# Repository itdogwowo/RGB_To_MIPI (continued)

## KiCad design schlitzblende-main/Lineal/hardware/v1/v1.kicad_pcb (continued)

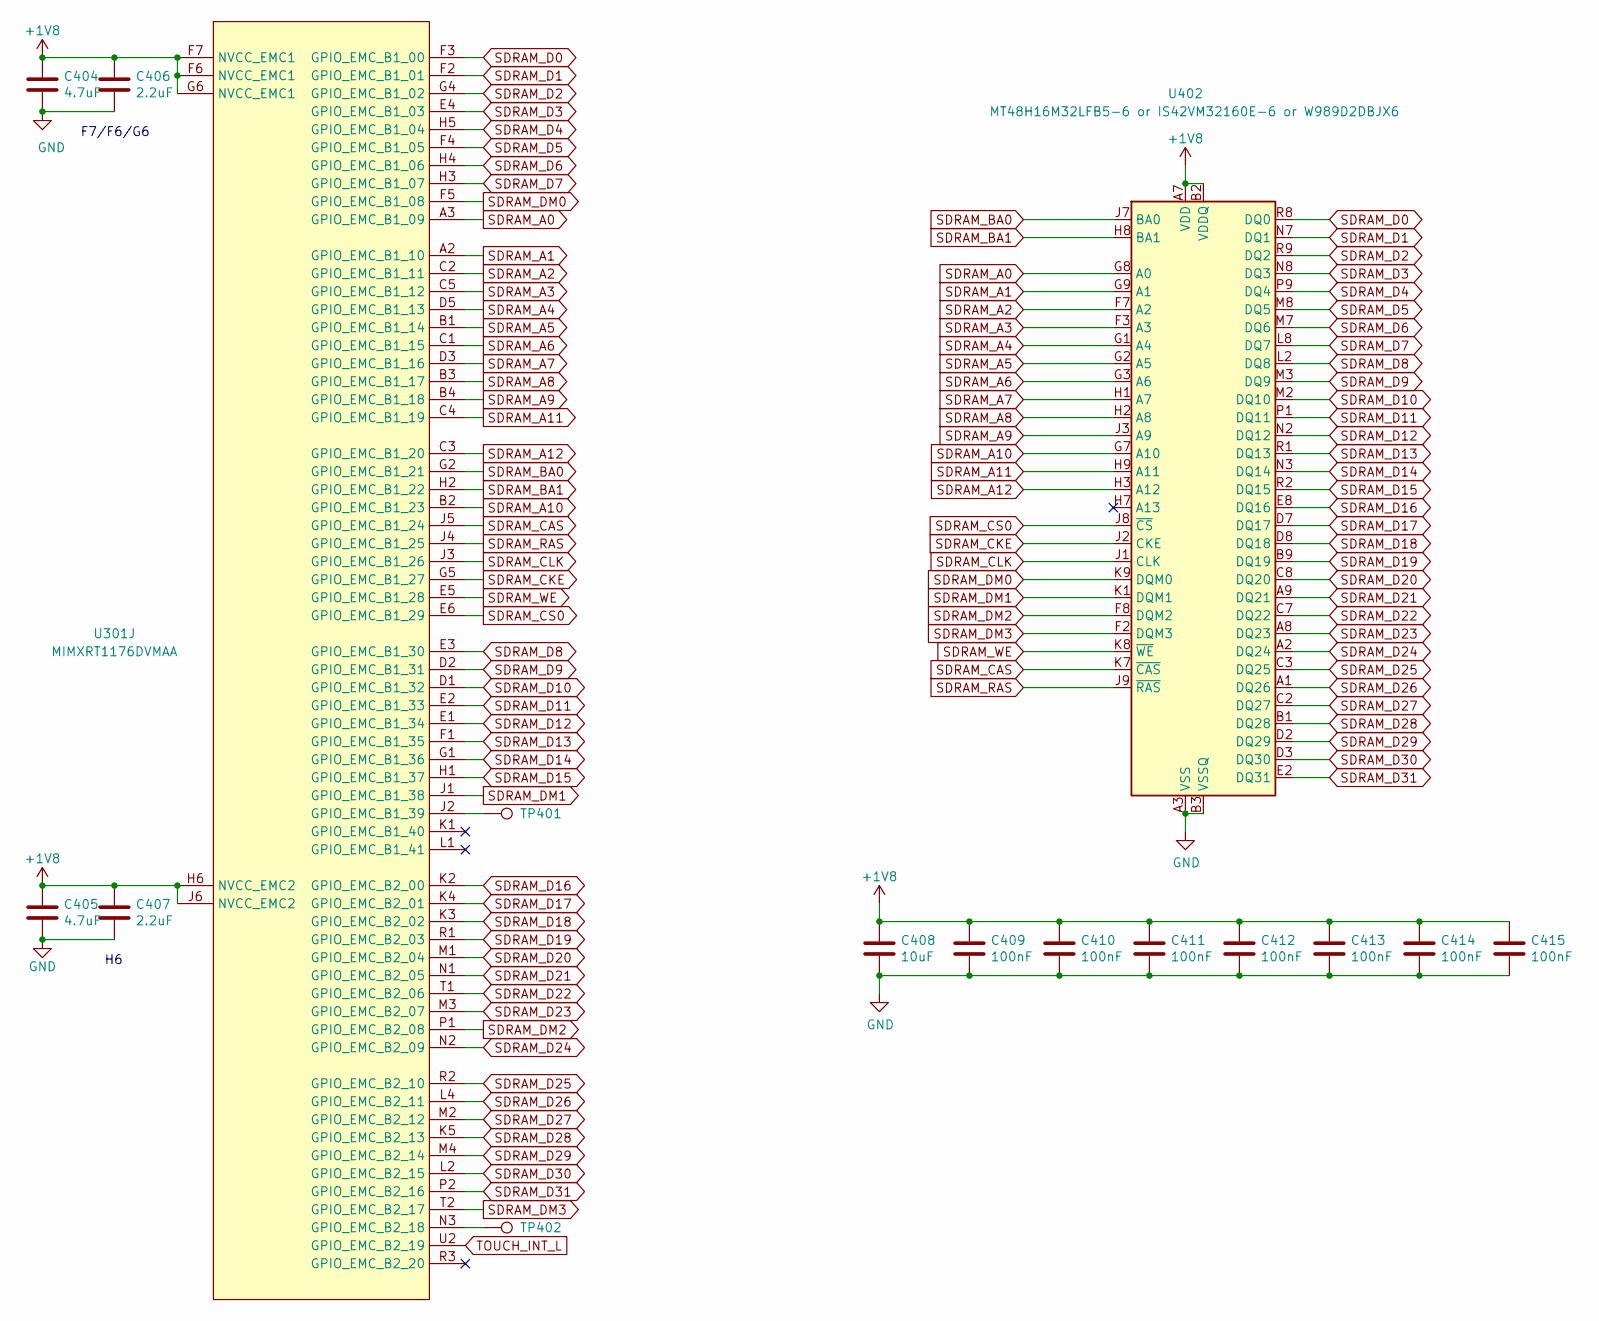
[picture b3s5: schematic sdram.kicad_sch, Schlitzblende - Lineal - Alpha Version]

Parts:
C404, C405: 4.7uF; C_0402_1005Metric
C406, C407: 2.2uF; C_0402_1005Metric
C408: 10uF; C_0402_1005Metric
C409, C410, C411, C412, C413, C414, C415: 100nF; C_0402_1005Metric
TP401: DQS; TestPoint_Pad_D0.5mm
TP402: DQS4; TestPoint_Pad_D0.5mm
U301: MIMXRT1176DVMAA; BGA-289_17x17_14.0x14.0mm
U402: MT48H16M32LFB5-6 or IS42VM32160E-6 or W989D2DBJX6; BGA-90_9x15_8.0x13.0mm

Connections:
+1V8: C404.1, C405.1, C406.1, C407.1, C408.1, C409.1, C410.1, C411.1, C412.1, C413.1, C414.1, C415.1, U301.F6 (NVCC_EMC1), U301.F7 (NVCC_EMC1), U301.G6 (NVCC_EMC1), U301.H6 (NVCC_EMC2), U301.J6 (NVCC_EMC2), U402.A7 (VDD), U402.B2 (VDDQ), U402.B7 (VDDQ), U402.C9 (VDDQ), U402.D9 (VDDQ), U402.E1 (VDDQ), U402.F9 (VDD), U402.L1 (VDDQ), U402.L7 (VDD), U402.M9 (VDDQ), U402.N9 (VDDQ), U402.P2 (VDDQ), U402.P7 (VDDQ), U402.R7 (VDD); also elsewhere on the board
unnamed: TP402.1, U301.N3 (GPIO_EMC_B2_18)
SDRAM_A0: U301.A3 (GPIO_EMC_B1_09), U402.G8 (A0)
SDRAM_A1: U301.A2 (GPIO_EMC_B1_10), U402.G9 (A1)
SDRAM_A2: U301.C2 (GPIO_EMC_B1_11), U402.F7 (A2)
SDRAM_A3: U301.C5 (GPIO_EMC_B1_12), U402.F3 (A3)
SDRAM_A4: U301.D5 (GPIO_EMC_B1_13), U402.G1 (A4)
SDRAM_A5: U301.B1 (GPIO_EMC_B1_14), U402.G2 (A5)
SDRAM_A6: U301.C1 (GPIO_EMC_B1_15), U402.G3 (A6)
SDRAM_A7: U301.D3 (GPIO_EMC_B1_16), U402.H1 (A7)
SDRAM_A8: U301.B3 (GPIO_EMC_B1_17), U402.H2 (A8)
SDRAM_A9: U301.B4 (GPIO_EMC_B1_18), U402.J3 (A9)
SDRAM_A10: U301.B2 (GPIO_EMC_B1_23), U402.G7 (A10)
SDRAM_A11: U301.C4 (GPIO_EMC_B1_19), U402.H9 (A11)
SDRAM_A12: U301.C3 (GPIO_EMC_B1_20), U402.H3 (A12)
SDRAM_BA0: U301.G2 (GPIO_EMC_B1_21), U402.J7 (BA0)
SDRAM_BA1: U301.H2 (GPIO_EMC_B1_22), U402.H8 (BA1)
SDRAM_CAS: U301.J5 (GPIO_EMC_B1_24), U402.K7 (~CAS)
SDRAM_CKE: U301.G5 (GPIO_EMC_B1_27), U402.J2 (CKE)
SDRAM_CLK: U301.J3 (GPIO_EMC_B1_26), U402.J1 (CLK)
SDRAM_CS0: U301.E6 (GPIO_EMC_B1_29), U402.J8 (~CS)
SDRAM_D0: U301.F3 (GPIO_EMC_B1_00), U402.R8 (DQ0)
SDRAM_D1: U301.F2 (GPIO_EMC_B1_01), U402.N7 (DQ1)
SDRAM_D2: U301.G4 (GPIO_EMC_B1_02), U402.R9 (DQ2)
SDRAM_D3: U301.E4 (GPIO_EMC_B1_03), U402.N8 (DQ3)
SDRAM_D4: U301.H5 (GPIO_EMC_B1_04), U402.P9 (DQ4)
SDRAM_D5: U301.F4 (GPIO_EMC_B1_05), U402.M8 (DQ5)
SDRAM_D6: U301.H4 (GPIO_EMC_B1_06), U402.M7 (DQ6)
SDRAM_D7: U301.H3 (GPIO_EMC_B1_07), U402.L8 (DQ7)
SDRAM_D8: U301.E3 (GPIO_EMC_B1_30), U402.L2 (DQ8)
SDRAM_D9: U301.D2 (GPIO_EMC_B1_31), U402.M3 (DQ9)
SDRAM_D10: U301.D1 (GPIO_EMC_B1_32), U402.M2 (DQ10)
SDRAM_D11: U301.E2 (GPIO_EMC_B1_33), U402.P1 (DQ11)
SDRAM_D12: U301.E1 (GPIO_EMC_B1_34), U402.N2 (DQ12)
SDRAM_D13: U301.F1 (GPIO_EMC_B1_35), U402.R1 (DQ13)
SDRAM_D14: U301.G1 (GPIO_EMC_B1_36), U402.N3 (DQ14)
SDRAM_D15: U301.H1 (GPIO_EMC_B1_37), U402.R2 (DQ15)
SDRAM_D16: U301.K2 (GPIO_EMC_B2_00), U402.E8 (DQ16)
SDRAM_D17: U301.K4 (GPIO_EMC_B2_01), U402.D7 (DQ17)
SDRAM_D18: U301.K3 (GPIO_EMC_B2_02), U402.D8 (DQ18)
SDRAM_D19: U301.R1 (GPIO_EMC_B2_03), U402.B9 (DQ19)
SDRAM_D20: U301.M1 (GPIO_EMC_B2_04), U402.C8 (DQ20)
SDRAM_D21: U301.N1 (GPIO_EMC_B2_05), U402.A9 (DQ21)
SDRAM_D22: U301.T1 (GPIO_EMC_B2_06), U402.C7 (DQ22)
SDRAM_D23: U301.M3 (GPIO_EMC_B2_07), U402.A8 (DQ23)
SDRAM_D24: U301.N2 (GPIO_EMC_B2_09), U402.A2 (DQ24)
SDRAM_D25: U301.R2 (GPIO_EMC_B2_10), U402.C3 (DQ25)
SDRAM_D26: U301.L4 (GPIO_EMC_B2_11), U402.A1 (DQ26)
SDRAM_D27: U301.M2 (GPIO_EMC_B2_12), U402.C2 (DQ27)
SDRAM_D28: U301.K5 (GPIO_EMC_B2_13), U402.B1 (DQ28)
SDRAM_D29: U301.M4 (GPIO_EMC_B2_14), U402.D2 (DQ29)
SDRAM_D30: U301.L2 (GPIO_EMC_B2_15), U402.D3 (DQ30)
SDRAM_D31: U301.P2 (GPIO_EMC_B2_16), U402.E2 (DQ31)
SDRAM_DM0: U301.F5 (GPIO_EMC_B1_08), U402.K9 (DQM0)
SDRAM_DM1: U301.J1 (GPIO_EMC_B1_38), U402.K1 (DQM1)
SDRAM_DM2: U301.P1 (GPIO_EMC_B2_08), U402.F8 (DQM2)
SDRAM_DM3: U301.T2 (GPIO_EMC_B2_17), U402.F2 (DQM3)
SDRAM_RAS: U301.J4 (GPIO_EMC_B1_25), U402.J9 (~RAS)
SDRAM_WE: U301.E5 (GPIO_EMC_B1_28), U402.K8 (~WE)
TOUCH_INT_L: U301.U2 (GPIO_EMC_B2_19); also elsewhere on the board

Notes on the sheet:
F7/F6/G6

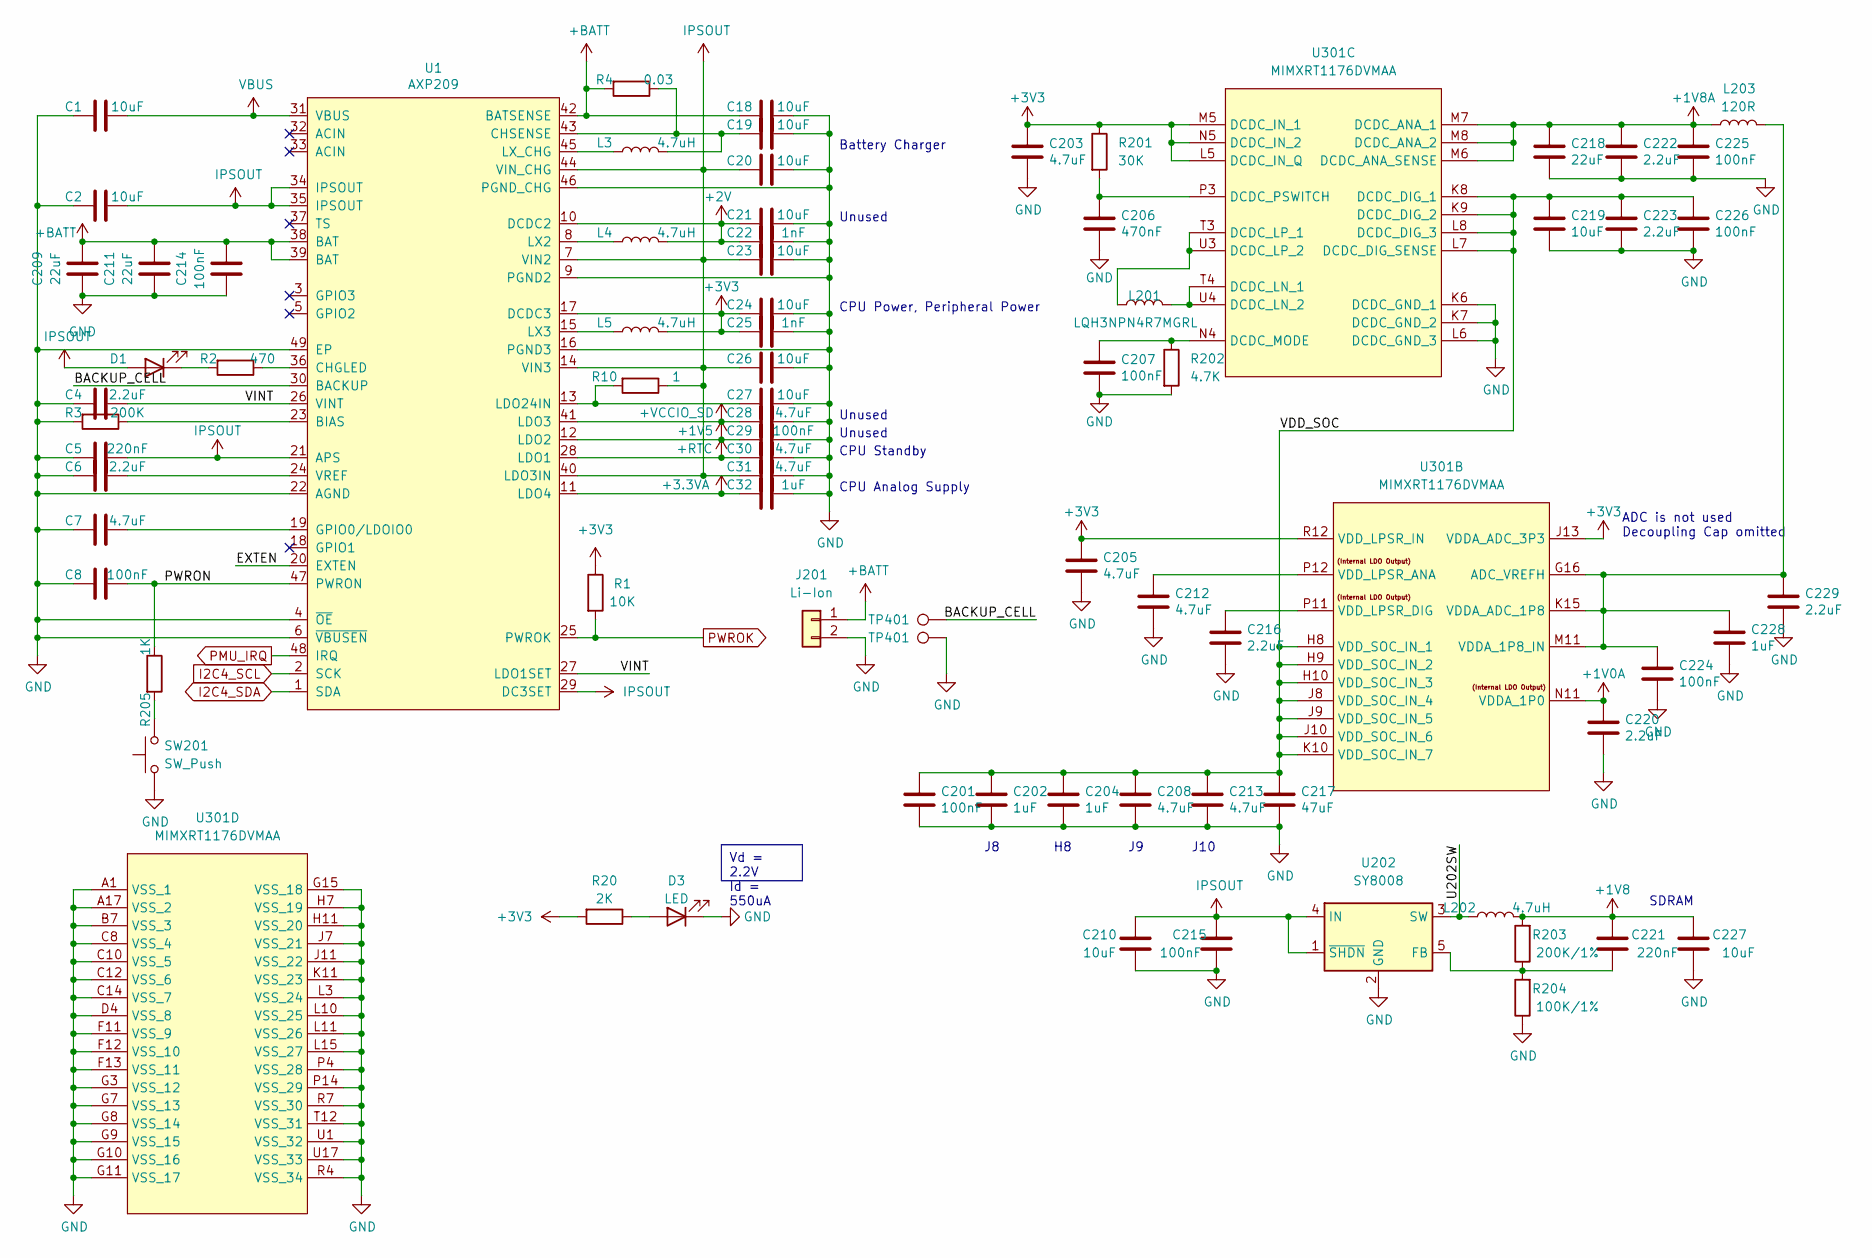
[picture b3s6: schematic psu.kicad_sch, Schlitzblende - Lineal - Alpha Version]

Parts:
C1, C2, C18, C19, C20, C21, C23, C24, C26, C27: 10uF; C_0603_1608Metric
C4, C6, C216, C220, C222, C223, C229: 2.2uF; C_0402_1005Metric
C5: 220nF; C_0402_1005Metric
C7, C28, C30, C31, C203, C205, C208, C212, C213: 4.7uF; C_0402_1005Metric
C8, C29, C201, C207, C224, C225, C226: 100nF; C_0402_1005Metric
C22, C25: 1nF; C_0402_1005Metric
C32, C202, C204, C228: 1uF; C_0402_1005Metric
C206: 470nF; C_0402_1005Metric
C209, C211: 22uF; C_0603_1608Metric; LCSC C116413
C210, C227: 10uF; C_0603_1608Metric; LCSC C105490
C214, C215: 100nF; C_0402_1005Metric; LCSC C56392
C217: 47uF; C_0603_1608Metric
C218: 22uF; C_0603_1608Metric
C219: 10uF; C_0402_1005Metric
C221: 220nF; C_0402_1005Metric; LCSC C880414
D1, D3: LED; D_0402_1005Metric
J201: Li-Ion; JST_ACH_BM02B-ACHSS-GAN-ETF_1x02-1MP_P1.20mm_Vertical
L3, L4, L5: 4.7uH; L_1212
L201: LQH3NPN4R7MGRL; L_1008_2520Metric
L202: 4.7uH; L_1212; LCSC C340379
L203: 120R; L_0402_1005Metric
R1: 10K; R_0402_1005Metric
R2: 470; R_0402_1005Metric
R3: 200K; R_0402_1005Metric
R4: 0.03; R_0402_1005Metric
R10: 1; R_0603_1608Metric
R20: 2K; R_0402_1005Metric
R201: 30K; R_0402_1005Metric
R202: 4.7K; R_0402_1005Metric
R203: 200K/1%; R_0402_1005Metric; LCSC C327350
R204: 100K/1%; R_0402_1005Metric; LCSC C138022
R205: 1K; R_0402_1005Metric
SW201: SW_Push; SW_SPST_TL3342
TP401: DQS; TestPoint_Pad_D0.5mm
U1: AXP209; QFN-48-1EP_6x6mm_P0.4mm_EP4.2x4.2mm_ThermalVias
U202: SY8008; TSOT-23-5; LCSC C82161
U301: MIMXRT1176DVMAA; BGA-289_17x17_14.0x14.0mm

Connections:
+1V0A: C220.1, U301.N11 (VDDA_1P0); also elsewhere on the board
+1V5: C29.2, U1.12 (LDO2)
+1V8: C221.2, C227.2, L202.2, R203.2; also elsewhere on the board
+1V8A: C218.1, C222.1, C225.1, L203.1, U301.M6 (DCDC_ANA_SENSE), U301.M7 (DCDC_ANA_1), U301.M8 (DCDC_ANA_2); also elsewhere on the board
+2V: C21.2, C22.2, L4.2, U1.10 (DCDC2)
+3.3VA: C32.2, U1.11 (LDO4)
+BATT: C18.2, C209.1, C211.1, C214.1, J201.1, R4.2, U1.38 (BAT), U1.39 (BAT), U1.42 (BATSENSE); also elsewhere on the board
+VCCIO_SD: C28.2, U1.41 (LDO3); also elsewhere on the board
/PSU/EXTEN: U1.20 (EXTEN)
/PSU/PWRON: C8.1, R205.1, U1.47 (PWRON)
/PSU/U202SW: L202.1, U202.3 (SW)
/PSU/VDD_SOC: C201.1, C202.1, C204.1, C208.1, C213.1, C217.1, C219.1, C223.1, C226.1, U301.H8 (VDD_SOC_IN_1), U301.H9 (VDD_SOC_IN_2), U301.H10 (VDD_SOC_IN_3), U301.J8 (VDD_SOC_IN_4), U301.J9 (VDD_SOC_IN_5), U301.J10 (VDD_SOC_IN_6), U301.K8 (DCDC_DIG_1), U301.K9 (DCDC_DIG_2), U301.K10 (VDD_SOC_IN_7), U301.L7 (DCDC_DIG_SENSE), U301.L8 (DCDC_DIG_3)
/PSU/VINT: C4.1, U1.26 (VINT), U1.27 (LDO1SET)
I2C4_SCL: U1.2 (SCK); also elsewhere on the board
I2C4_SDA: U1.1 (SDA); also elsewhere on the board
IPSOUT: C2.1, C5.1, C20.2, C23.2, C26.2, C31.2, C210.2, C215.2, D1.2 (A), R10.1, U1.7 (VIN2), U1.14 (VIN3), U1.21 (APS), U1.29 (DC3SET), U1.34 (IPSOUT), U1.35 (IPSOUT), U1.40 (LDO3IN), U1.44 (VIN_CHG), U202.1 (~SHDN), U202.4 (IN)
unnamed: D1.1 (K), R2.2
unnamed: D3.2 (A), R20.1
unnamed: R3.1, U1.23 (BIAS)
unnamed: R2.1, U1.36 (CHGLED)
unnamed: C19.2, L3.2, R4.1, U1.43 (CHSENSE)
unnamed: C7.1, U1.19 (GPIO0/LDOIO0)
unnamed: C27.2, R10.2, U1.13 (LDO24IN)
unnamed: L4.1, U1.8 (LX2)
unnamed: L5.1, U1.15 (LX3)
unnamed: L3.1, U1.45 (LX_CHG)
unnamed: C6.1, U1.24 (VREF)
unnamed: C221.1, R203.1, R204.2, U202.5 (FB)
unnamed: C224.1, C228.1, C229.1, L203.2, U301.G16 (ADC_VREFH), U301.K15 (VDDA_ADC_1P8), U301.M11 (VDDA_1P8_IN)
unnamed: C212.1, U301.P12 (VDD_LPSR_ANA)
unnamed: C216.1, U301.P11 (VDD_LPSR_DIG)
unnamed: L201.2, U301.T4 (DCDC_LN_1), U301.U4 (DCDC_LN_2)
unnamed: L201.1, U301.T3 (DCDC_LP_1), U301.U3 (DCDC_LP_2)
unnamed: C207.1, R202.1, U301.N4 (DCDC_MODE)
unnamed: C206.1, R201.2, U301.P3 (DCDC_PSWITCH)
PMU_IRQ: U1.48 (IRQ); also elsewhere on the board
PWROK: R1.2, U1.25 (PWROK); also elsewhere on the board
VBUS: C1.1, U1.31 (VBUS); also elsewhere on the board

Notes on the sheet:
Vd = 2.2V Id = 550uA
Unused
CPU Standby
Battery Charger
J10
SDRAM
CPU Power, Peripheral Power
ADC is not used Decoupling Cap omitted
CPU Analog Supply

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
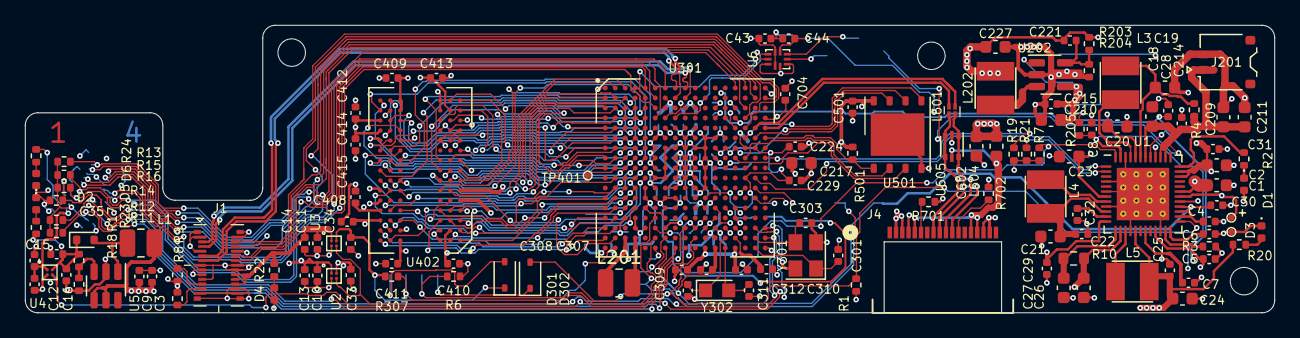
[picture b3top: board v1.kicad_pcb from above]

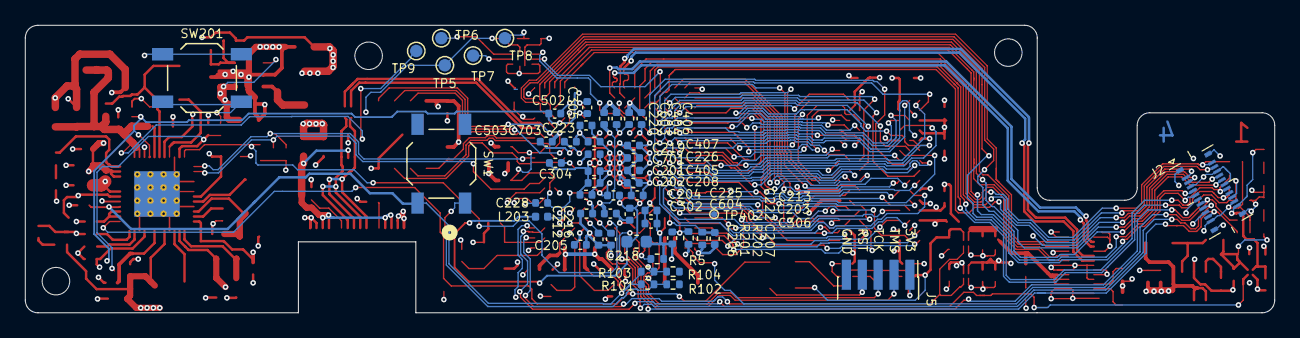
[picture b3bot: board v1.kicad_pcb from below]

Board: 4 copper layers, 100.0 x 23.0 mm, 184 parts (51 on the bottom side), 165 nets.

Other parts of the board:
C16: 1uF; C_0402_1005Metric
D4, D5, D6: LED; D_0402_1005Metric
R22: 2K; R_0402_1005Metric
R23, R24: 3.3K; R_0402_1005Metric
SW1: SW_Push; SW_SPST_TL3342
TP1, TP2: DQS; TestPoint_Pad_D0.5mm

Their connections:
unnamed: D4.2 (A), R22.1
unnamed: D5.2 (A), R23.1
unnamed: D6.2 (A), R24.1

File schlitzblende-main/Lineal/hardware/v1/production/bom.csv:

Designator,Footprint,Quantity,Value,LCSC Part #
"C1, C18, C19, C2, C20, C21, C210, C227, C23, C24, C26, C27, C602",0603,13,10uF,
"C10, C11, C12, C16, C202, C204, C228, C3, C307, C308, C32, C603, C604, C701, C703, C704",0402,16,1uF,
"C13, C14, C15, C33, C34, C35",0402,6,0.1uF,
"C201, C207, C214, C215, C224, C225, C226, C29, C312, C409, C410, C411, C412, C413, C414, C415, C43, C44, C8, C9",0402,20,100nF,
"C203, C205, C208, C212, C213, C28, C30, C31, C404, C405, C7",0402,11,4.7uF,
"C206, C310, C501",0402,3,470nF,
"C209, C211, C218",0603,3,22uF,C116413
"C216, C220, C222, C223, C229, C302, C304, C305, C306, C4, C406, C407, C502, C503, C6",0402,15,2.2uF,
C217,0603,1,47uF,
"C219, C408",0402,2,10uF,
"C22, C25",0402,2,1nF,
"C221, C5",0402,2,220nF,C880414
"C301, C303, C309, C311",0402,4,18pF,
"D1, D3, D4, D5, D6",0402,5,LED,
D2,D_SOD-523,1,B0530WS,
"D301, D302",D_SOD-323,2,B0540W,
"H1, H3, H4",MountingHole_2.2mm_M2_DIN965,3,MountingHole,
J1,DF40PG(1.5)-26DS-04V,1,DF40PG(1.5)-26DS-04V,
J2,AA07-S022VA1-Mockup,1,AA07-S022VA1,
J201,JST_ACH_BM02B-ACHSS-GAN-ETF_1x02-1MP_P1.20mm_Vertical,1,Li-Ion,
J4,CX90M-16P_HIR,1,CX90M-16P,
J5,PinHeader_1x05_P1.27mm_Vertical_SMD,1,Conn_01x05_Pin,
L1,1008,1,4.7uH,
L201,L_Vishay_IHLP-1212,1,LQH3NPN4R7MGRL,
"L202, L3, L4, L5",L_1212,4,4.7uH,C340379 
L203,0402,1,120R,
L601,L_CommonModeChoke_Panasonic_EXC14CE,1,EXC14CE900U,
L604,0603,1,120R,
"R1, R102, R104, R19, R21, R307, R6",0402,7,10K,
R10,0603,1,1,
"R101, R103",0402,2,DNP,
R11,0402,1,NC,
"R12, R13, R14, R15, R16, R202, R5, R8, R9",0402,9,4.7K,
"R17, R203",0402,2,200K/1%,
R18,0402,1,27K/1%,
R2,0402,1,470,
"R20, R22",0402,2,2K,
R201,0402,1,30K,
R204,0402,1,100K/1%,C138022
R205,0402,1,1K,
"R23, R24",0402,2,3.3K,
R3,0402,1,200K,
R4,0402,1,0.03,
R501,0402,1,100K,
R7,0402,1,51K,
"R701, R702",0402,2,5.1K/1%,
"SW1, SW201",SW_SPST_TL3342,2,SW_Push,
"TP1, TP2, TP401",TestPoint_Pad_D0.5mm,3,DQS,
TP402,TestPoint_Pad_D0.5mm,1,DQS4,
TP5,TestPoint_Pad_D1.0mm,1,3V3,
TP6,TestPoint_Pad_D1.0mm,1,TXD,
TP7,TestPoint_Pad_D1.0mm,1,RXD,
TP8,TestPoint_Pad_D1.0mm,1,GND,
TP9,TestPoint_Pad_D1.0mm,1,Battery,
U1,QFN-48-1EP_6x6mm_P0.4mm_EP4.2x4.2mm_ThermalVias,1,AXP209,
"U2, U3, U4",WLCSP-4_0.8x0.8mm_P0.4mm,3,TCK106AG,
U202,TSOT-23-5,1,SY8008,C82161
U301,BGA-289_17x17_14.0x14.0mm,1,MIMXRT1176DVMAA,
U402,BGA-90_9x15_8.0x13.0mm,1,MT48H16M32LFB5-6 or IS42VM32160E-6 or W989D2DBJX6,
U5,SOT-23-6,1,SY7208,
U501,WSON-8-1EP_6x5mm_P1.27mm_EP3.4x4.3mm,1,W25Q128FW,
U6,UQFN-10_1.4x1.8mm_P0.4mm,1,SN74AXC2T245,
U605,SOT-666,1,USBLC6-2P6,
Y301,Oscillator_SMD_Abracon_ASE-4Pin_3.2x2.5mm,1,24MHz,
Y302,Crystal_SMD_TXC_9HT11-2Pin_2.0x1.2mm_HandSoldering,1,32.768K,
